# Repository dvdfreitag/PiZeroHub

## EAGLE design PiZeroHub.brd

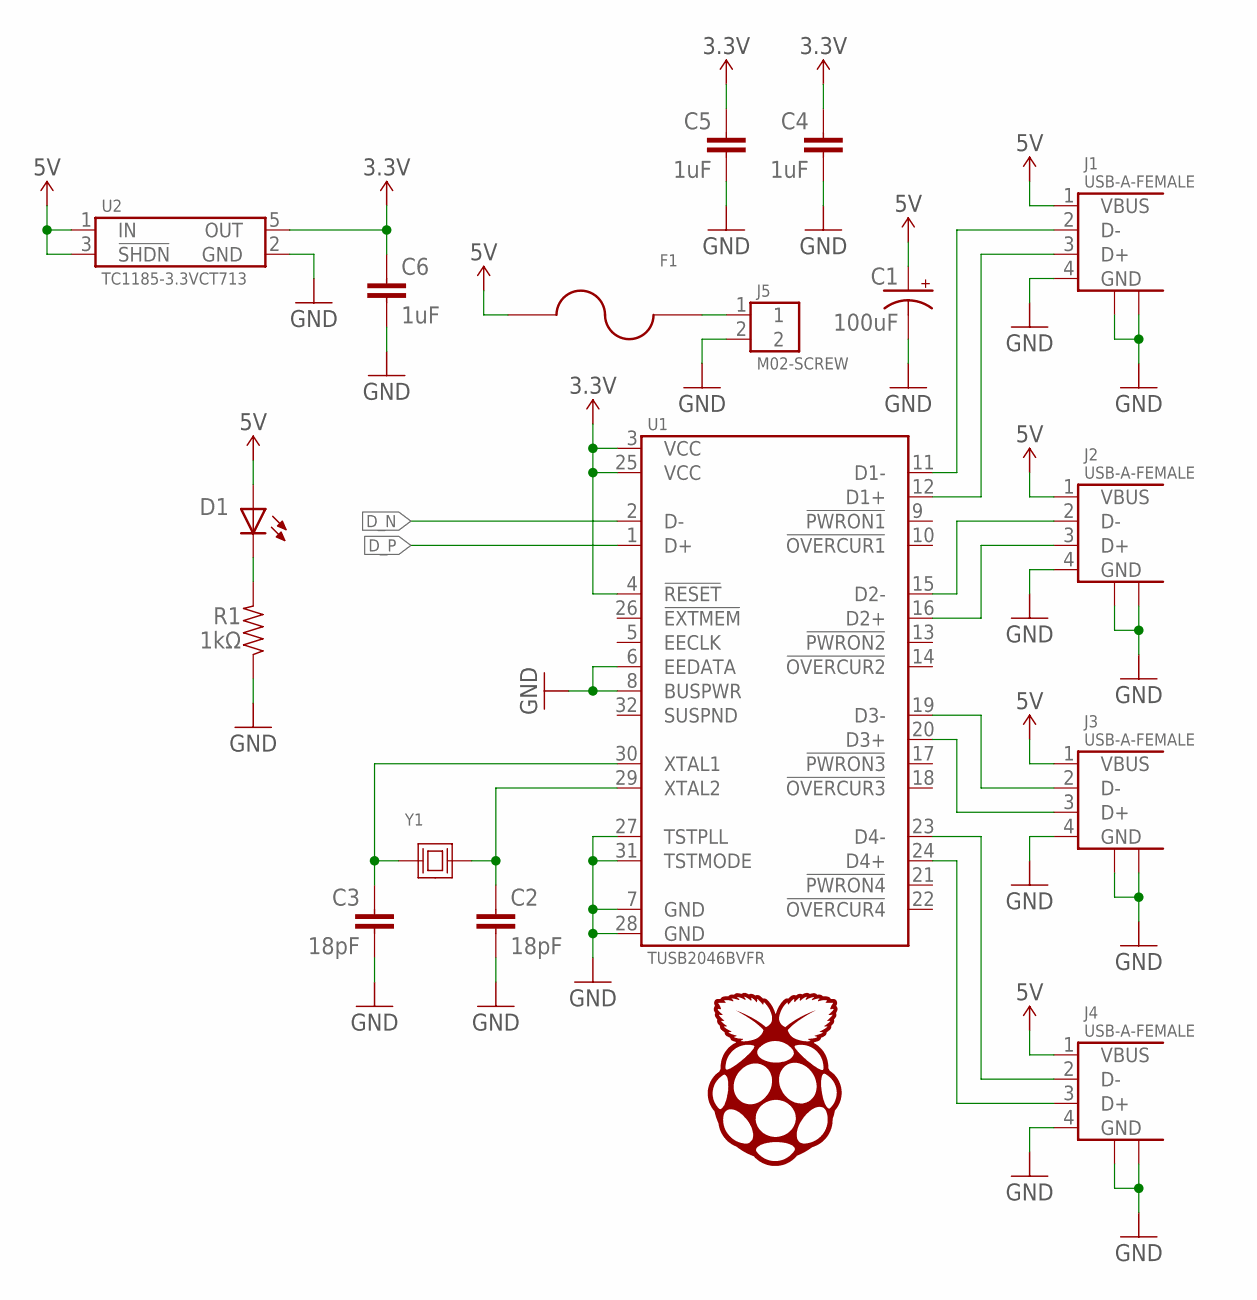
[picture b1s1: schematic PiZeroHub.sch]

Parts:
C1: 100uF; CAP_POL-6.6X6.6
C2, C3: 18pF; 0805-CAP
C4, C5, C6: 1uF; 0805-CAP
D1: LED-0805; 0805-LED
F1: PTC-1812; 1812-PTC
J1, J2, J3, J4: USB-A-FEMALE
J5: M02-SCREW
R1: 1kΩ; 0805-RES
U1: TUSB2046BVFR; LQFP-32
U2: TC1185-3.3VCT713; SOT23-5
U$1: RPI-ZERO_NOPAD; RPI_ZERO-NOPADS
Y1: CRYSTAL2-HC49; HC49/US

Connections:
3.3V: C4.1, C5.1, C6.1, U1.3 (VCC), U1.4 (!RESET), U1.25 (VCC), U2.5 (OUT)
5V: C1.+, D1.A, F1.2, J1.1 (VBUS), J2.1 (VBUS), J3.1 (VBUS), J4.1 (VBUS), U2.1 (IN), U2.3 (!SHDN)
D1_N: J1.2 (D-), U1.11 (D1-)
D1_P: J1.3 (D+), U1.12 (D1+)
D2_N: J2.2 (D-), U1.15 (D2-)
D2_P: J2.3 (D+), U1.16 (D2+)
D3_N: J3.2 (D-), U1.19 (D3-)
D3_P: J3.3 (D+), U1.20 (D3+)
D4_N: J4.2 (D-), U1.23 (D4-)
D4_P: J4.3 (D+), U1.24 (D4+)
D_N: U1.2 (D-)
D_P: U1.1 (D+)
GND: C1.-, C2.2, C3.2, C4.2, C5.2, C6.2, J1.4 (GND), J1.P$1, J1.P$2, J2.4 (GND), J2.P$1, J2.P$2, J3.4 (GND), J3.P$1, J3.P$2, J4.4 (GND), J4.P$1, J4.P$2, J5.2, R1.1, U1.6 (EEDATA), U1.7 (GND), U1.8 (BUSPWR), U1.27 (TSTPLL), U1.28 (GND), U1.31 (TSTMODE), U2.2 (GND)
unnamed: D1.C, R1.2
unnamed: F1.1, J5.1
unnamed: C3.1, U1.30 (XTAL1), Y1.1
unnamed: C2.1, U1.29 (XTAL2), Y1.2

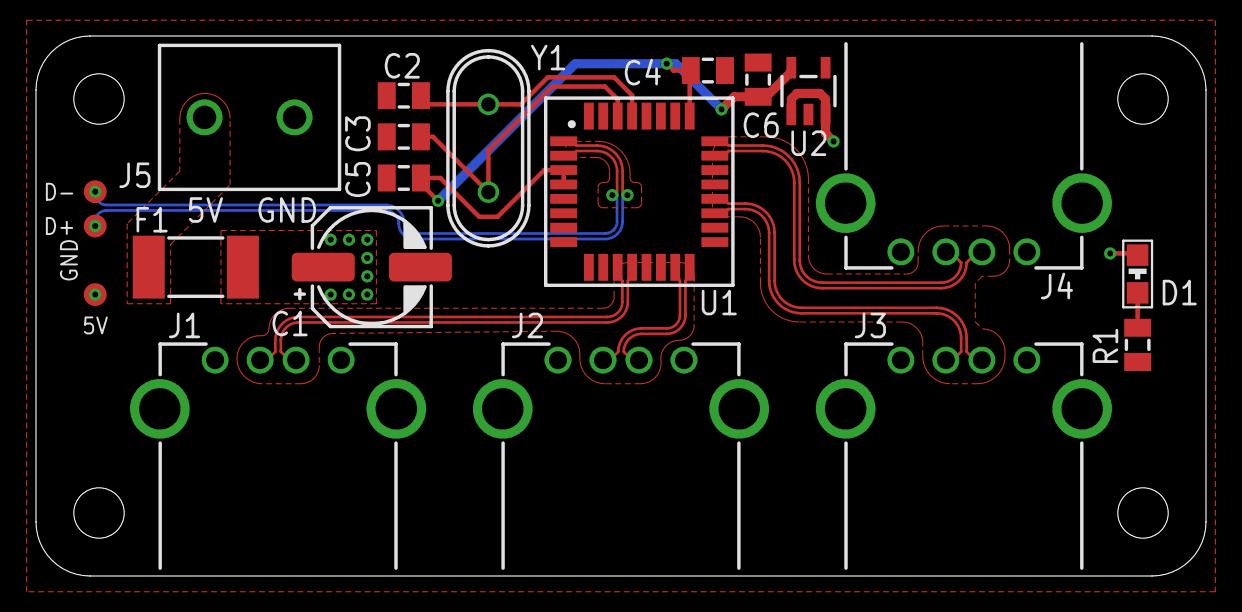
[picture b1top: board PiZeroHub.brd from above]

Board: 2 copper layers, 65.0 x 30.0 mm, 18 parts (0 on the bottom side), 15 nets.

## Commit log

2016-08-11 Create LICENSE
